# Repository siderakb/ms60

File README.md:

# MS60 Keybaord

60%-size keyboard.

Stabilizer footprints from [ebastler/marbastlib](https://github.com/ebastler/marbastlib).

## License

Licensed under [CERN-OHL-P v2](/LICENSE).

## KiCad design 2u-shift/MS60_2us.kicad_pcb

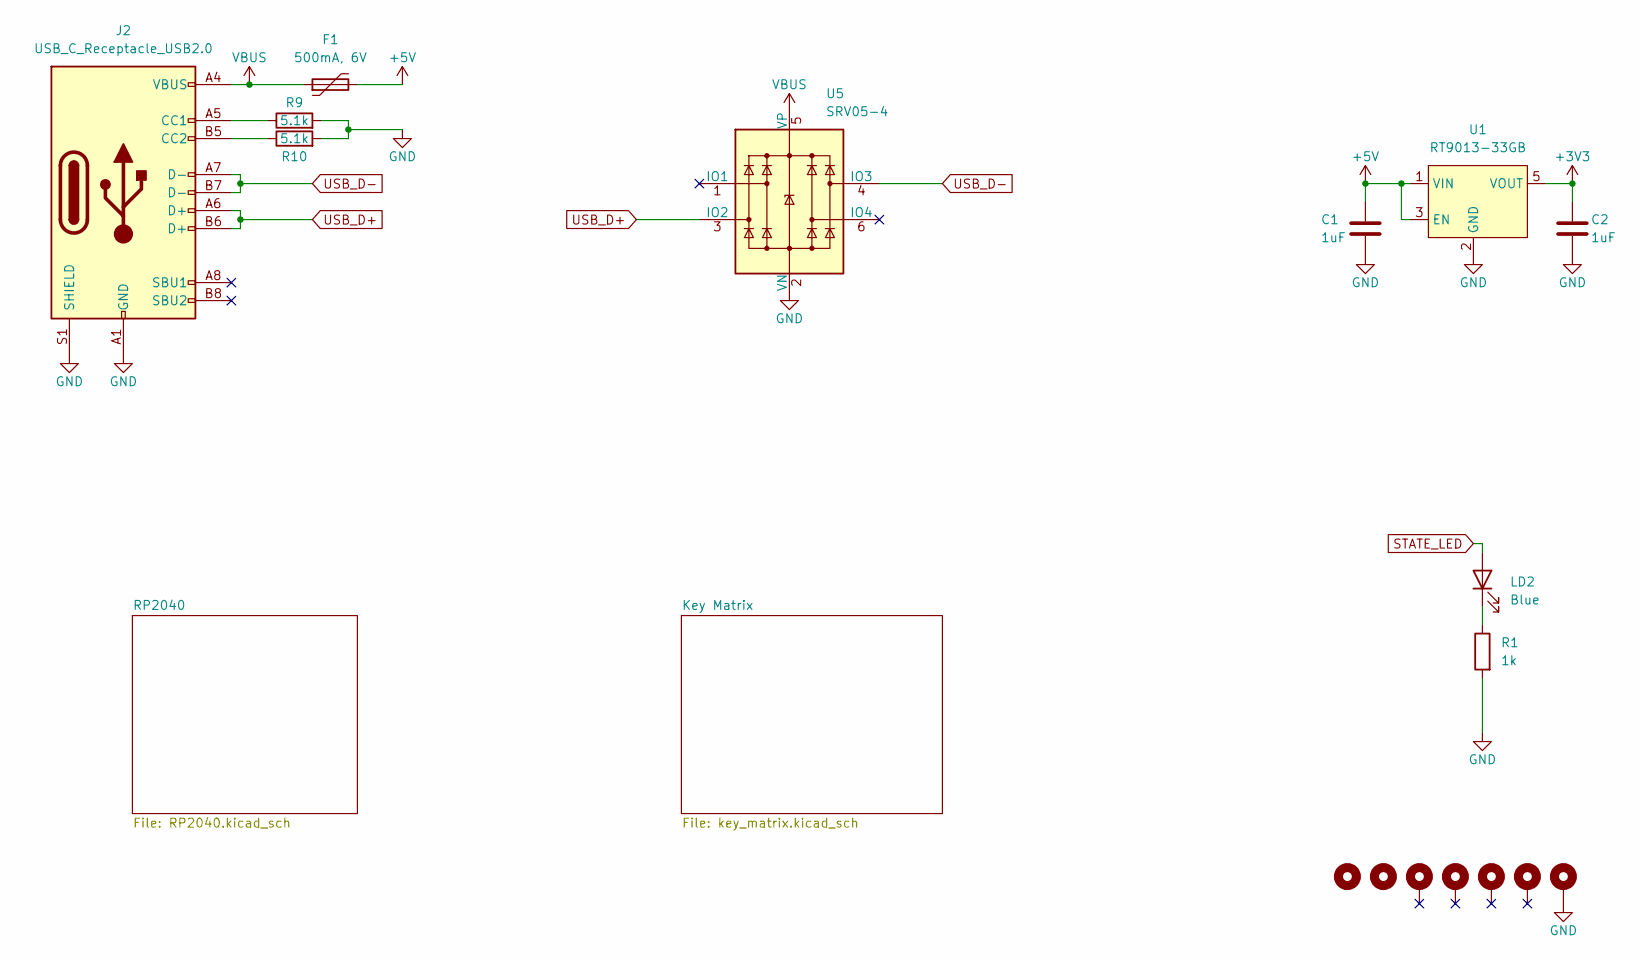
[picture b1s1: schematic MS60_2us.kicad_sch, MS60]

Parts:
C1, C2: 1uF; C_0402_1005Metric; MFR. Part # CL05A105KA5NQNC; LCSC C52923
F1: 500mA, 6V; Fuse_0805_2012Metric; MFR. Part # SMD0805B050TF; LCSC C269104
H1, H7: MountingHole_Pad; MountingHole-D
H2, H3: MountingHole_Pad; MountingHole-A
H4: MountingHole_Pad; MountingHole-B
H5, H6: MountingHole; MountingHole-C
J2: USB_C_Receptacle_USB2.0; USB_C_Receptacle_HRO_TYPE-C-31-M-12; MFR. Part # TYPE-C-31-M-12; LCSC C165948
LD2: Blue; LED_0603_1608Metric; MFR. Part # 19-217/GHC-YR1S2/3T; LCSC C72043
R1: 1k; R_0402_1005Metric; MFR. Part # 0402WGF1001TCE; LCSC C11702
R9, R10: 5.1k; R_0603_1608Metric; MFR. Part # 0402WGF5101TCE; LCSC C25905
U1: RT9013-33GB; SOT-23-5; MFR. Part # TPRT9013-33GB; LCSC C587158
U5: SRV05-4; SOT-23-6; MFR. Part # SRV05-4-P-T7; LCSC C85364

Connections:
+3V3: C2.1, U1.5 (VOUT); also elsewhere on the board
+5V: C1.1, F1.2, U1.1 (VIN), U1.3 (EN)
GND: C1.2, C2.2, H4.1, J2.A1 (GND), J2.A12 (GND), J2.B1 (GND), J2.B12 (GND), J2.S1 (SHIELD), R1.2, R9.2, R10.2, U1.2 (GND), U5.2 (VN); also elsewhere on the board
unnamed: J2.A5 (CC1), R9.1
unnamed: J2.B5 (CC2), R10.1
unnamed: LD2.1 (K), R1.1
STATE_LED: LD2.2 (A); also elsewhere on the board
USB_D+: J2.A6 (D+), J2.B6 (D+), U5.3 (IO2); also elsewhere on the board
USB_D-: J2.A7 (D-), J2.B7 (D-), U5.4 (IO3); also elsewhere on the board
VBUS: F1.1, J2.A4 (VBUS), J2.A9 (VBUS), J2.B4 (VBUS), J2.B9 (VBUS), U5.5 (VP)

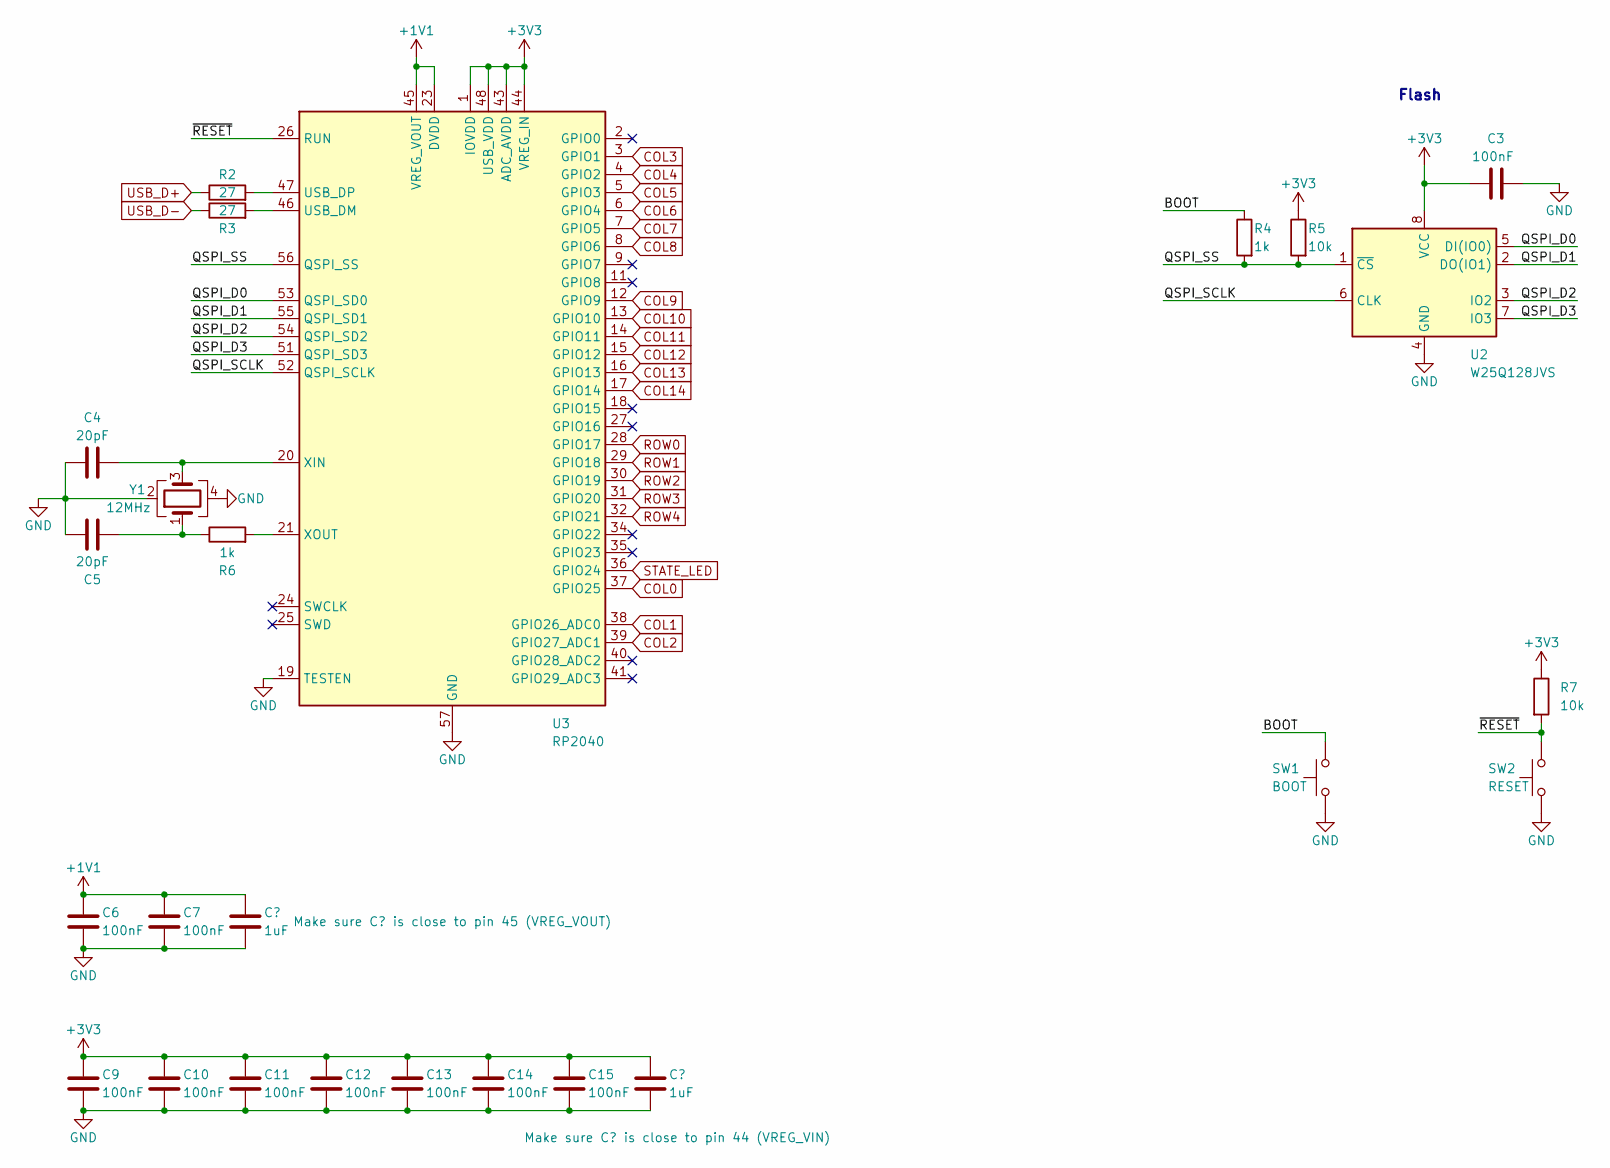
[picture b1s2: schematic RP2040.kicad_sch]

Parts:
C3, C6, C7, C9, C10, C11, C12, C13, C14, C15: 100nF; C_0402_1005Metric; MFR. Part # CL05B104KO5NNNC; LCSC C1525
C4, C5: 20pF; C_0402_1005Metric; MFR. Part # 0402CG200J500NT; LCSC C1554
C8, C16: 1uF; C_0402_1005Metric; MFR. Part # CL05A105KA5NQNC; LCSC C52923
R2, R3: 27; R_0603_1608Metric; MFR. Part # 0603WAF270JT5E; LCSC C25190
R4, R6: 1k; R_0402_1005Metric; MFR. Part # 0402WGF1001TCE; LCSC C11702
R5, R7: 10k; R_0402_1005Metric; MFR. Part # 0402WGF1002TCE; LCSC C25744
SW1: BOOT; SW_SPST_TL3342; MFR. Part # TS-1064S-A1B2-D4; LCSC C498294
SW2: RESET; SW_SPST_TL3342; MFR. Part # TS-1064S-A1B2-D4; LCSC C498294
U2: W25Q128JVS; SOIC-8_5.23x5.23mm_P1.27mm; MFR. Part # W25Q128JVSIQ; LCSC C97521
U3: RP2040; QFN-56-1EP_7x7mm_P0.4mm_EP3.2x3.2mm; MFR. Part # RP2040; LCSC C2040
Y1: 12MHz; Crystal_SMD_3225-4Pin_3.2x2.5mm; MFR. Part # X322512MSB4SI; LCSC C9002

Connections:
+1V1: C6.1, C7.1, C8.1, U3.23 (DVDD), U3.45 (VREG_VOUT), U3.50 (DVDD)
+3V3: C3.1, C9.1, C10.1, C11.1, C12.1, C13.1, C14.1, C15.1, C16.1, R5.1, R7.1, U2.8 (VCC), U3.1 (IOVDD), U3.10 (IOVDD), U3.22 (IOVDD), U3.33 (IOVDD), U3.42 (IOVDD), U3.43 (ADC_AVDD), U3.44 (VREG_IN), U3.48 (USB_VDD), U3.49 (IOVDD); also elsewhere on the board
/RP2040/BOOT: R4.1, SW1.2
/RP2040/QSPI_D0: U2.5 (DI(IO0)), U3.53 (QSPI_SD0)
/RP2040/QSPI_D1: U2.2 (DO(IO1)), U3.55 (QSPI_SD1)
/RP2040/QSPI_D2: U2.3 (IO2), U3.54 (QSPI_SD2)
/RP2040/QSPI_D3: U2.7 (IO3), U3.51 (QSPI_SD3)
/RP2040/QSPI_SCLK: U2.6 (CLK), U3.52 (QSPI_SCLK)
/RP2040/QSPI_SS: R4.2, R5.2, U2.1 (~CS), U3.56 (QSPI_SS)
/RP2040/~RESET: R7.2, SW2.2, U3.26 (RUN)
COL0: U3.37 (GPIO25); also elsewhere on the board
COL1: U3.38 (GPIO26_ADC0); also elsewhere on the board
COL2: U3.39 (GPIO27_ADC1); also elsewhere on the board
COL3: U3.3 (GPIO1); also elsewhere on the board
COL4: U3.4 (GPIO2); also elsewhere on the board
COL5: U3.5 (GPIO3); also elsewhere on the board
COL6: U3.6 (GPIO4); also elsewhere on the board
COL7: U3.7 (GPIO5); also elsewhere on the board
COL8: U3.8 (GPIO6); also elsewhere on the board
COL9: U3.12 (GPIO9); also elsewhere on the board
COL10: U3.13 (GPIO10); also elsewhere on the board
COL11: U3.14 (GPIO11); also elsewhere on the board
COL12: U3.15 (GPIO12); also elsewhere on the board
COL13: U3.16 (GPIO13); also elsewhere on the board
COL14: U3.17 (GPIO14); also elsewhere on the board
GND: C3.2, C4.1, C5.1, C6.2, C7.2, C8.2, C9.2, C10.2, C11.2, C12.2, C13.2, C14.2, C15.2, C16.2, SW1.1, SW2.1, U2.4 (GND), U3.19 (TESTEN), U3.57 (GND), Y1.2, Y1.4; also elsewhere on the board
unnamed: C5.2, R6.1, Y1.1
unnamed: R3.2, U3.46 (USB_DM)
unnamed: R2.2, U3.47 (USB_DP)
unnamed: C4.2, U3.20 (XIN), Y1.3
unnamed: R6.2, U3.21 (XOUT)
ROW0: U3.28 (GPIO17); also elsewhere on the board
ROW1: U3.29 (GPIO18); also elsewhere on the board
ROW2: U3.30 (GPIO19); also elsewhere on the board
ROW3: U3.31 (GPIO20); also elsewhere on the board
ROW4: U3.32 (GPIO21); also elsewhere on the board
STATE_LED: U3.36 (GPIO24); also elsewhere on the board
USB_D+: R2.1; also elsewhere on the board
USB_D-: R3.1; also elsewhere on the board

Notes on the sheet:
Flash

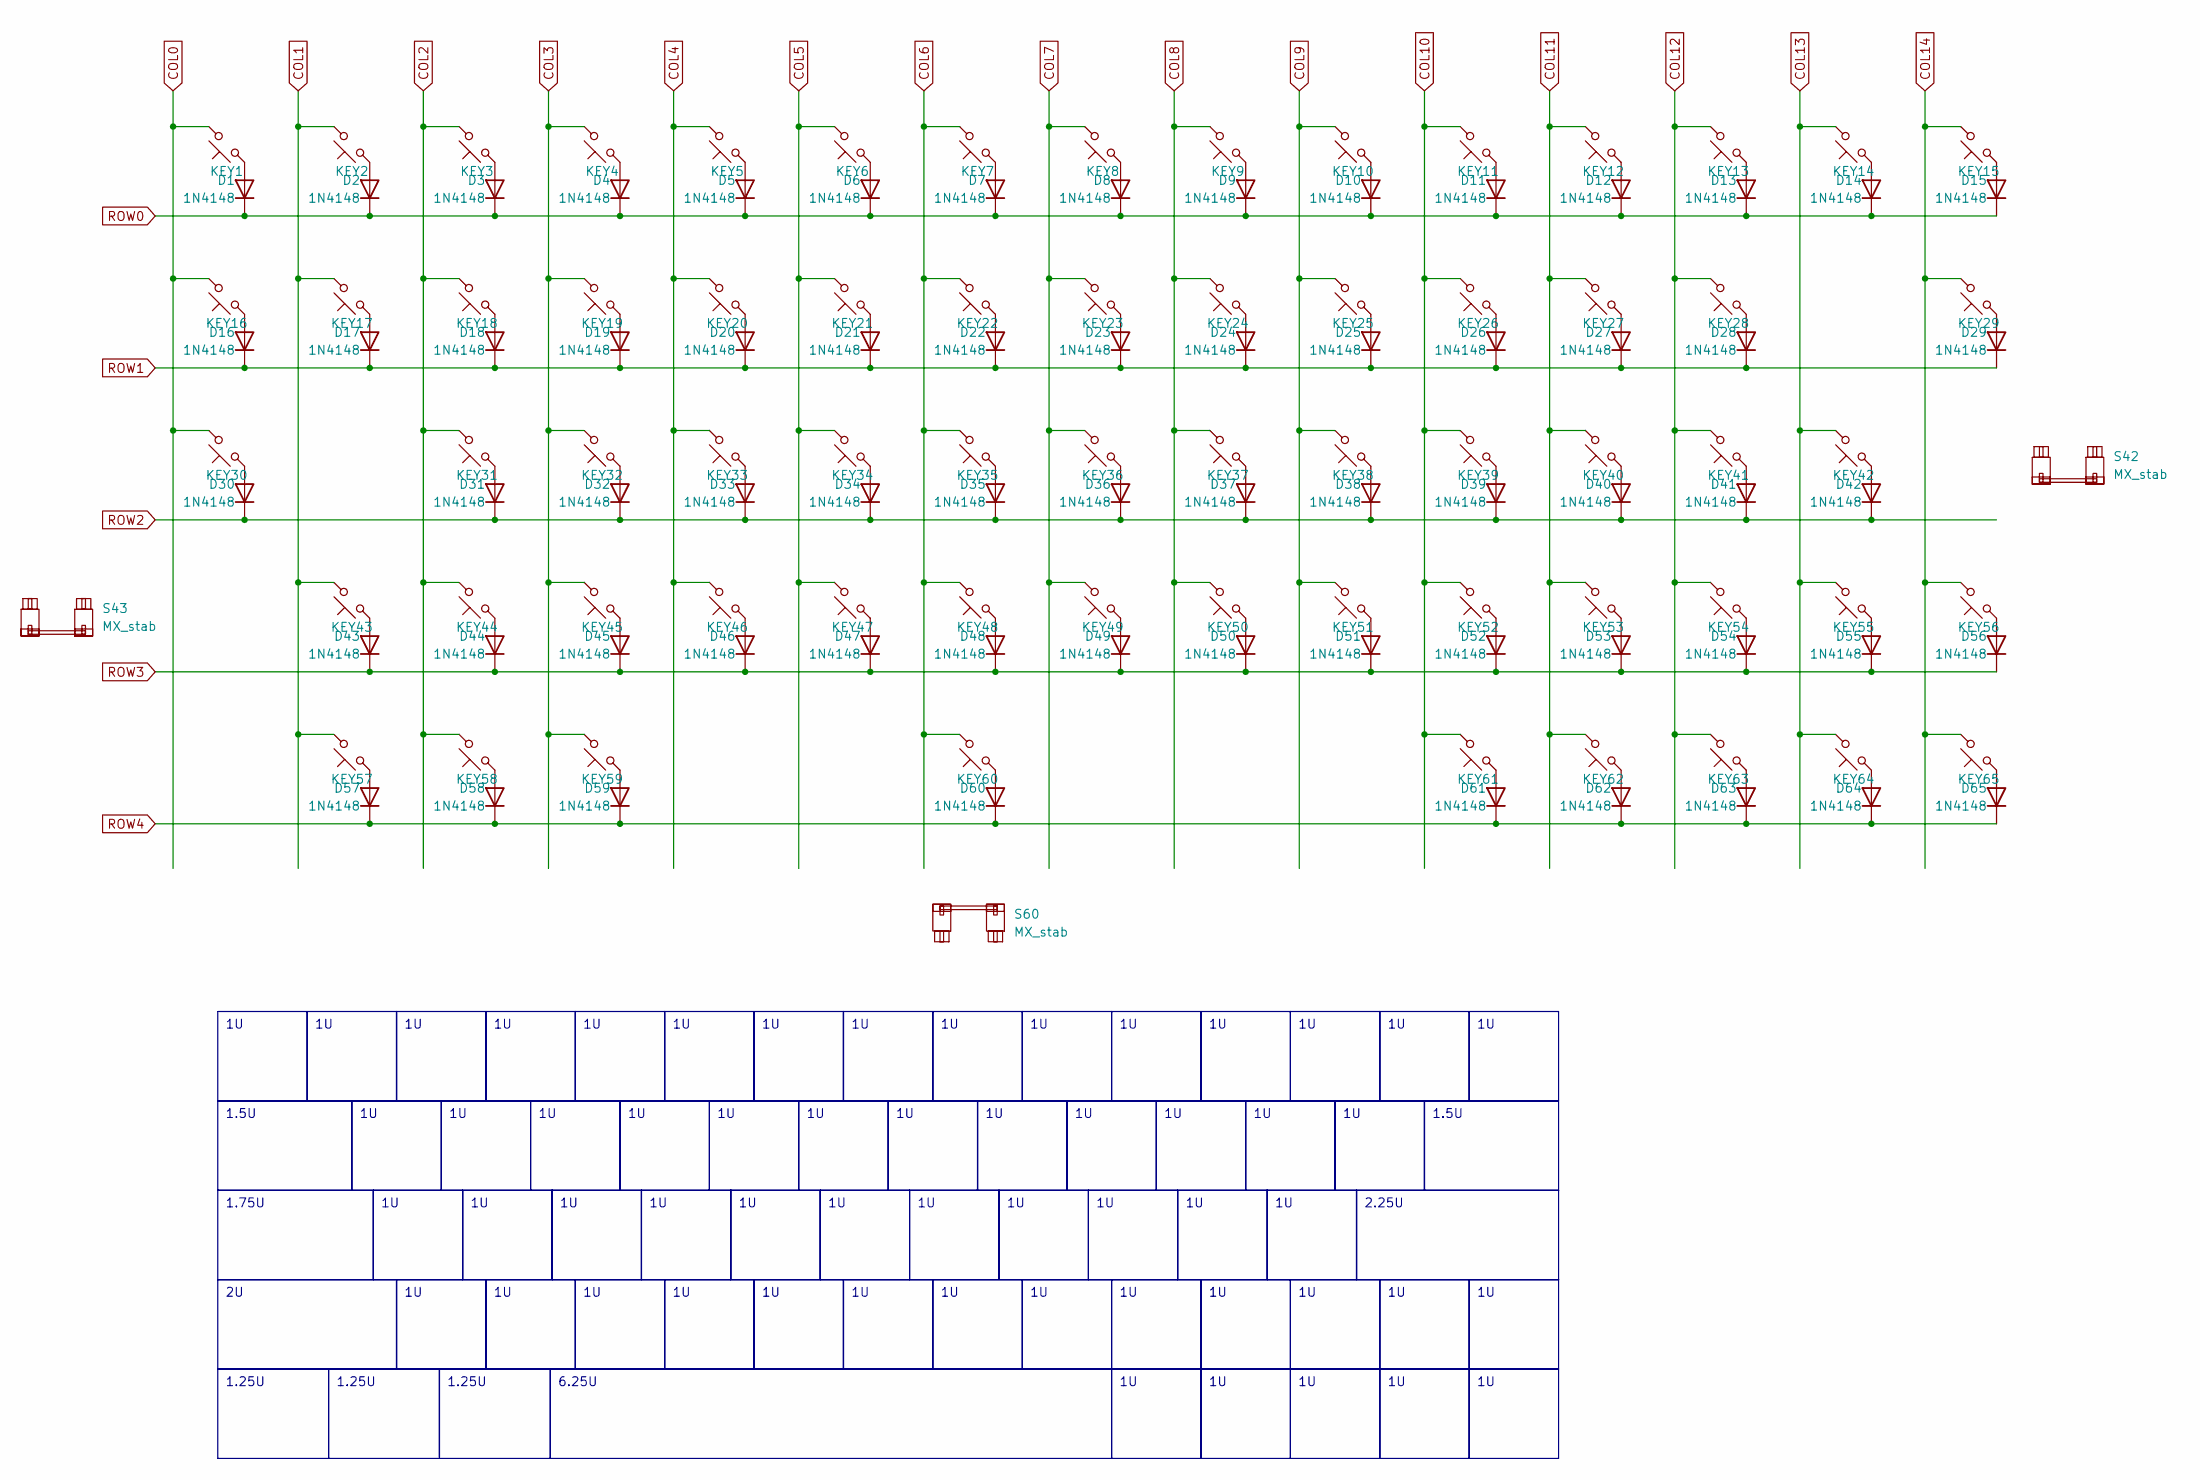
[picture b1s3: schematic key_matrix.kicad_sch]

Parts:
D1, D2, D3, D4, D5, D6, D7, D8, D9, D10, D11, D12, D13, D14, D15, D16, D17, D18, D19, D20, D21, D22, D23, D24, D25, D26, D27, D28, D29, D30, D31, D32, D33, D34, D35, D36, D37, D38, D39, D40, D41, D42, D43, D44, D45, D46, D47, D48, D49, D50, D51, D52, D53, D54, D55, D56, D57, D58, D59, D60, D61, D62, D63, D64, D65: 1N4148; D_SOD-323_HandSoldering; MFR. Part # 1N4148W; LCSC C81598
KEY1, KEY2, KEY3, KEY4, KEY5, KEY6, KEY7, KEY8, KEY9, KEY10, KEY11, KEY12, KEY13, KEY14, KEY15, KEY16, KEY17, KEY18, KEY19, KEY20, KEY21, KEY22, KEY23, KEY24, KEY25, KEY26, KEY27, KEY28, KEY29, KEY30, KEY31, KEY32, KEY33, KEY34, KEY35, KEY36, KEY37, KEY38, KEY39, KEY40, KEY41, KEY42, KEY43, KEY44, KEY45, KEY46, KEY47, KEY48, KEY49, KEY50, KEY51, KEY52, KEY53, KEY54, KEY55, KEY56, KEY57, KEY58, KEY59, KEY60, KEY61, KEY62, KEY63, KEY64, KEY65: SW_Push_45deg; SW_MX_HotSwap_PTH_nSilk
S42: MX_stab; STAB_MX_2.25u
S43: MX_stab; STAB_MX_2u
S60: MX_stab; STAB_MX_6.25u

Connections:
COL0: KEY1.2, KEY16.2, KEY30.2; also elsewhere on the board
COL1: KEY2.2, KEY17.2, KEY43.2, KEY57.2; also elsewhere on the board
COL2: KEY3.2, KEY18.2, KEY31.2, KEY44.2, KEY58.2; also elsewhere on the board
COL3: KEY4.2, KEY19.2, KEY32.2, KEY45.2, KEY59.2; also elsewhere on the board
COL4: KEY5.2, KEY20.2, KEY33.2, KEY46.2; also elsewhere on the board
COL5: KEY6.2, KEY21.2, KEY34.2, KEY47.2; also elsewhere on the board
COL6: KEY7.2, KEY22.2, KEY35.2, KEY48.2, KEY60.2; also elsewhere on the board
COL7: KEY8.2, KEY23.2, KEY36.2, KEY49.2; also elsewhere on the board
COL8: KEY9.2, KEY24.2, KEY37.2, KEY50.2; also elsewhere on the board
COL9: KEY10.2, KEY25.2, KEY38.2, KEY51.2; also elsewhere on the board
COL10: KEY11.2, KEY26.2, KEY39.2, KEY52.2, KEY61.2; also elsewhere on the board
COL11: KEY12.2, KEY27.2, KEY40.2, KEY53.2, KEY62.2; also elsewhere on the board
COL12: KEY13.2, KEY28.2, KEY41.2, KEY54.2, KEY63.2; also elsewhere on the board
COL13: KEY14.2, KEY42.2, KEY55.2, KEY64.2; also elsewhere on the board
COL14: KEY15.2, KEY29.2, KEY56.2, KEY65.2; also elsewhere on the board
unnamed: D1.2 (A), KEY1.1
unnamed: D2.2 (A), KEY2.1
unnamed: D3.2 (A), KEY3.1
unnamed: D4.2 (A), KEY4.1
unnamed: D5.2 (A), KEY5.1
unnamed: D6.2 (A), KEY6.1
unnamed: D7.2 (A), KEY7.1
unnamed: D8.2 (A), KEY8.1
unnamed: D9.2 (A), KEY9.1
unnamed: D10.2 (A), KEY10.1
unnamed: D11.2 (A), KEY11.1
unnamed: D12.2 (A), KEY12.1
unnamed: D13.2 (A), KEY13.1
unnamed: D14.2 (A), KEY14.1
unnamed: D15.2 (A), KEY15.1
unnamed: D16.2 (A), KEY16.1
unnamed: D17.2 (A), KEY17.1
unnamed: D18.2 (A), KEY18.1
unnamed: D19.2 (A), KEY19.1
unnamed: D20.2 (A), KEY20.1
unnamed: D21.2 (A), KEY21.1
unnamed: D22.2 (A), KEY22.1
unnamed: D23.2 (A), KEY23.1
unnamed: D24.2 (A), KEY24.1
unnamed: D25.2 (A), KEY25.1
unnamed: D26.2 (A), KEY26.1
unnamed: D27.2 (A), KEY27.1
unnamed: D28.2 (A), KEY28.1
unnamed: D29.2 (A), KEY29.1
unnamed: D30.2 (A), KEY30.1
unnamed: D31.2 (A), KEY31.1
unnamed: D32.2 (A), KEY32.1
unnamed: D33.2 (A), KEY33.1
unnamed: D34.2 (A), KEY34.1
unnamed: D35.2 (A), KEY35.1
unnamed: D36.2 (A), KEY36.1
unnamed: D37.2 (A), KEY37.1
unnamed: D38.2 (A), KEY38.1
unnamed: D39.2 (A), KEY39.1
unnamed: D40.2 (A), KEY40.1
unnamed: D41.2 (A), KEY41.1
unnamed: D42.2 (A), KEY42.1
unnamed: D43.2 (A), KEY43.1
unnamed: D44.2 (A), KEY44.1
unnamed: D45.2 (A), KEY45.1
unnamed: D46.2 (A), KEY46.1
unnamed: D47.2 (A), KEY47.1
unnamed: D48.2 (A), KEY48.1
unnamed: D49.2 (A), KEY49.1
unnamed: D50.2 (A), KEY50.1
unnamed: D51.2 (A), KEY51.1
unnamed: D52.2 (A), KEY52.1
unnamed: D53.2 (A), KEY53.1
unnamed: D54.2 (A), KEY54.1
unnamed: D55.2 (A), KEY55.1
unnamed: D56.2 (A), KEY56.1
unnamed: D57.2 (A), KEY57.1
unnamed: D58.2 (A), KEY58.1
unnamed: D59.2 (A), KEY59.1
unnamed: D60.2 (A), KEY60.1
unnamed: D61.2 (A), KEY61.1
unnamed: D62.2 (A), KEY62.1
unnamed: D63.2 (A), KEY63.1
unnamed: D64.2 (A), KEY64.1
unnamed: D65.2 (A), KEY65.1
ROW0: D1.1 (K), D2.1 (K), D3.1 (K), D4.1 (K), D5.1 (K), D6.1 (K), D7.1 (K), D8.1 (K), D9.1 (K), D10.1 (K), D11.1 (K), D12.1 (K), D13.1 (K), D14.1 (K), D15.1 (K); also elsewhere on the board
ROW1: D16.1 (K), D17.1 (K), D18.1 (K), D19.1 (K), D20.1 (K), D21.1 (K), D22.1 (K), D23.1 (K), D24.1 (K), D25.1 (K), D26.1 (K), D27.1 (K), D28.1 (K), D29.1 (K); also elsewhere on the board
ROW2: D30.1 (K), D31.1 (K), D32.1 (K), D33.1 (K), D34.1 (K), D35.1 (K), D36.1 (K), D37.1 (K), D38.1 (K), D39.1 (K), D40.1 (K), D41.1 (K), D42.1 (K); also elsewhere on the board
ROW3: D43.1 (K), D44.1 (K), D45.1 (K), D46.1 (K), D47.1 (K), D48.1 (K), D49.1 (K), D50.1 (K), D51.1 (K), D52.1 (K), D53.1 (K), D54.1 (K), D55.1 (K), D56.1 (K); also elsewhere on the board
ROW4: D57.1 (K), D58.1 (K), D59.1 (K), D60.1 (K), D61.1 (K), D62.1 (K), D63.1 (K), D64.1 (K), D65.1 (K); also elsewhere on the board

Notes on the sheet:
1.5U
2.25U
1.25U
6.25U
1.75U

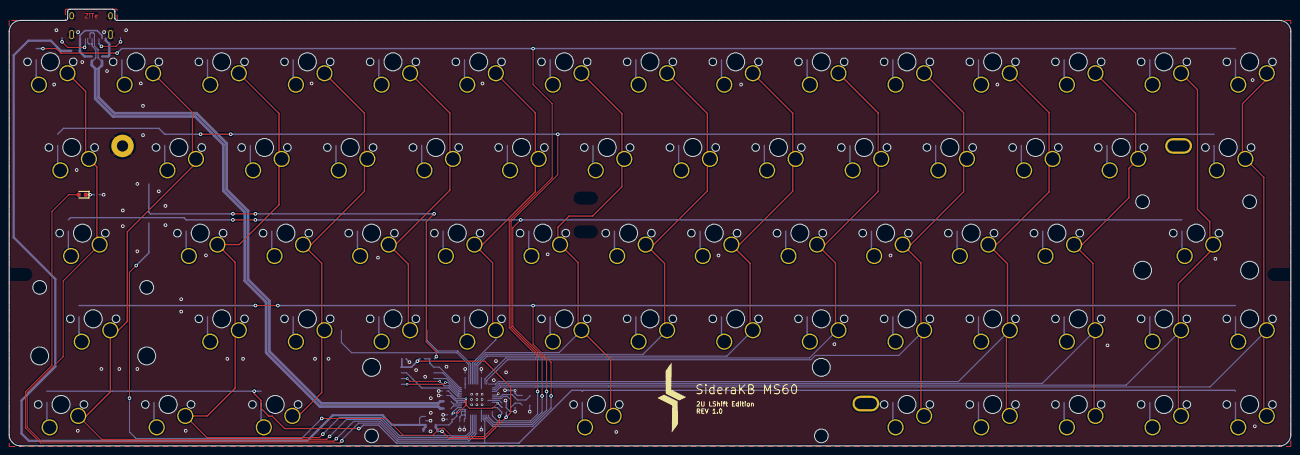
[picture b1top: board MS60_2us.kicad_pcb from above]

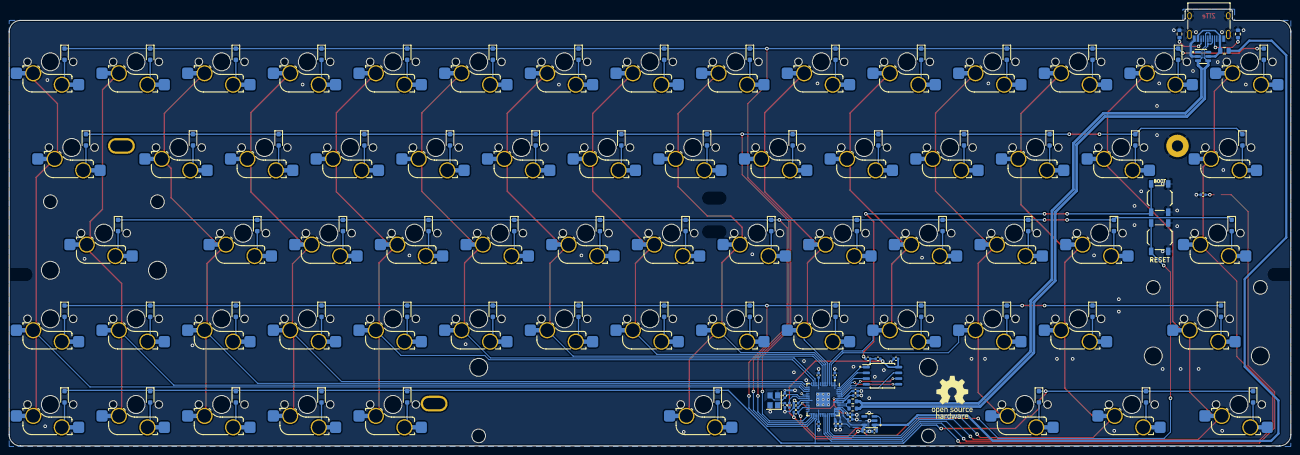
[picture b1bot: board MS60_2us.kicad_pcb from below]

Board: 2 copper layers, 285.0 x 97.1 mm, 175 parts (99 on the bottom side), 109 nets.

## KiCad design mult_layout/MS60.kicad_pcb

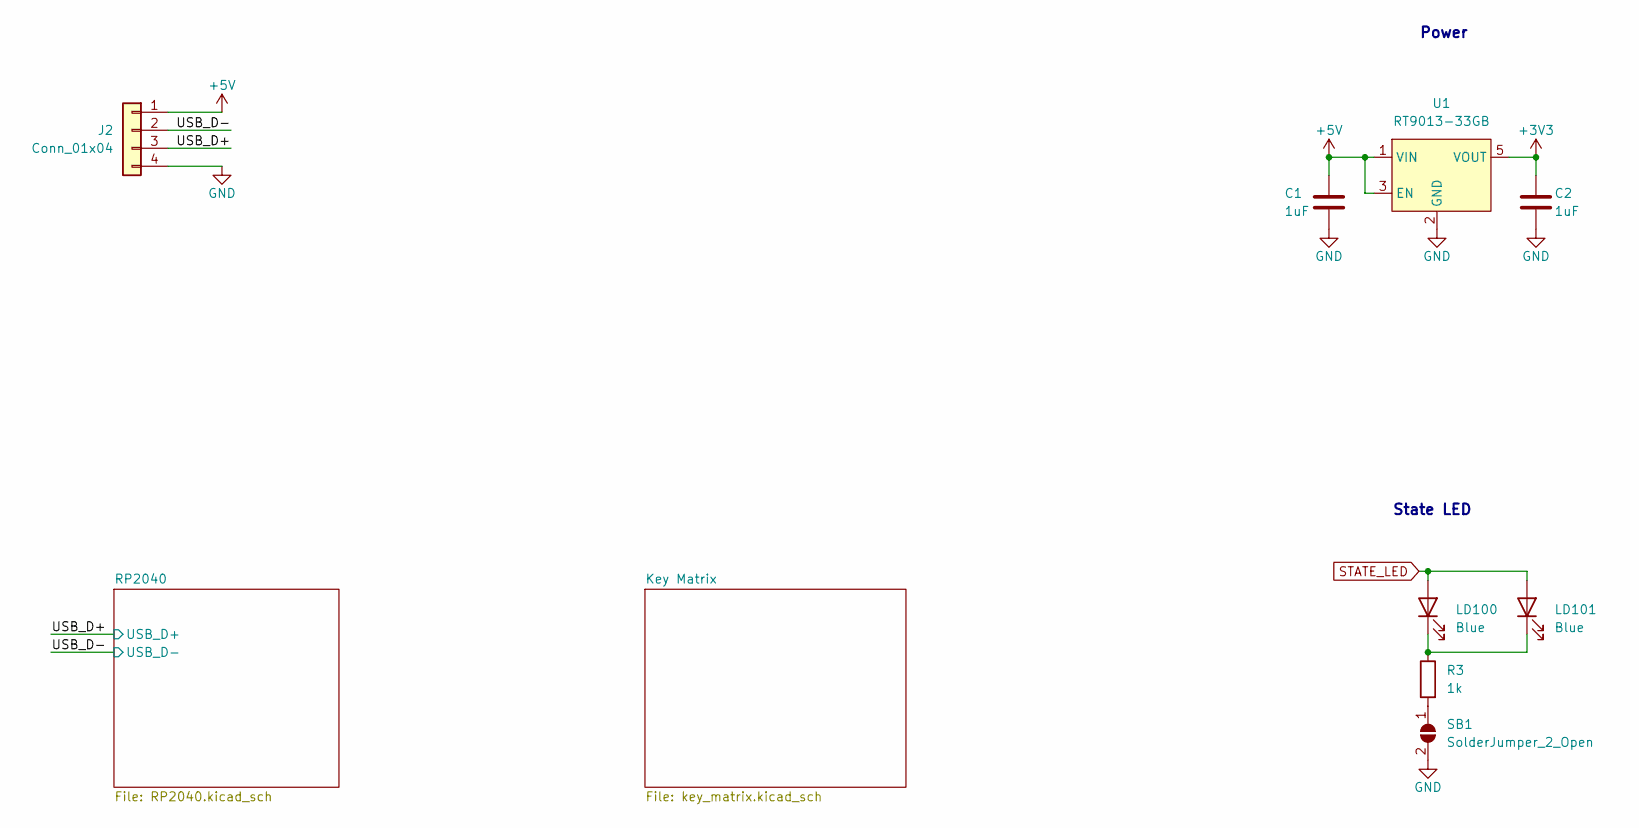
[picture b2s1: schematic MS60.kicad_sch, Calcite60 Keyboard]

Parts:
C1, C2: 1uF; C_0402_1005Metric; MFR. Part # CL05A105KA5NQNC; LCSC C52923
J2: Conn_01x04; Molex_Pico-EZmate_78171-0004_1x04-1MP_P1.20mm_Vertical
LD100, LD101: Blue; LED_0603_1608Metric; MFR. Part # 19-217/GHC-YR1S2/3T; LCSC C72043
R3: 1k; R_0402_1005Metric; MFR. Part # 0402WGF1001TCE; LCSC C11702
SB1: SolderJumper_2_Open; SolderJumper-2_P1.3mm_Open_TrianglePad1.0x1.5mm
U1: RT9013-33GB; SOT-23-5; MFR. Part # TPRT9013-33GB; LCSC C587158

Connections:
/USB_D+: J2.3; also elsewhere on the board
/USB_D-: J2.2; also elsewhere on the board
unnamed: LD100.1 (K), LD101.1 (K), R3.1
unnamed: R3.2, SB1.1 (A)
STATE_LED: LD100.2 (A), LD101.2 (A); also elsewhere on the board

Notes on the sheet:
State LED
Power

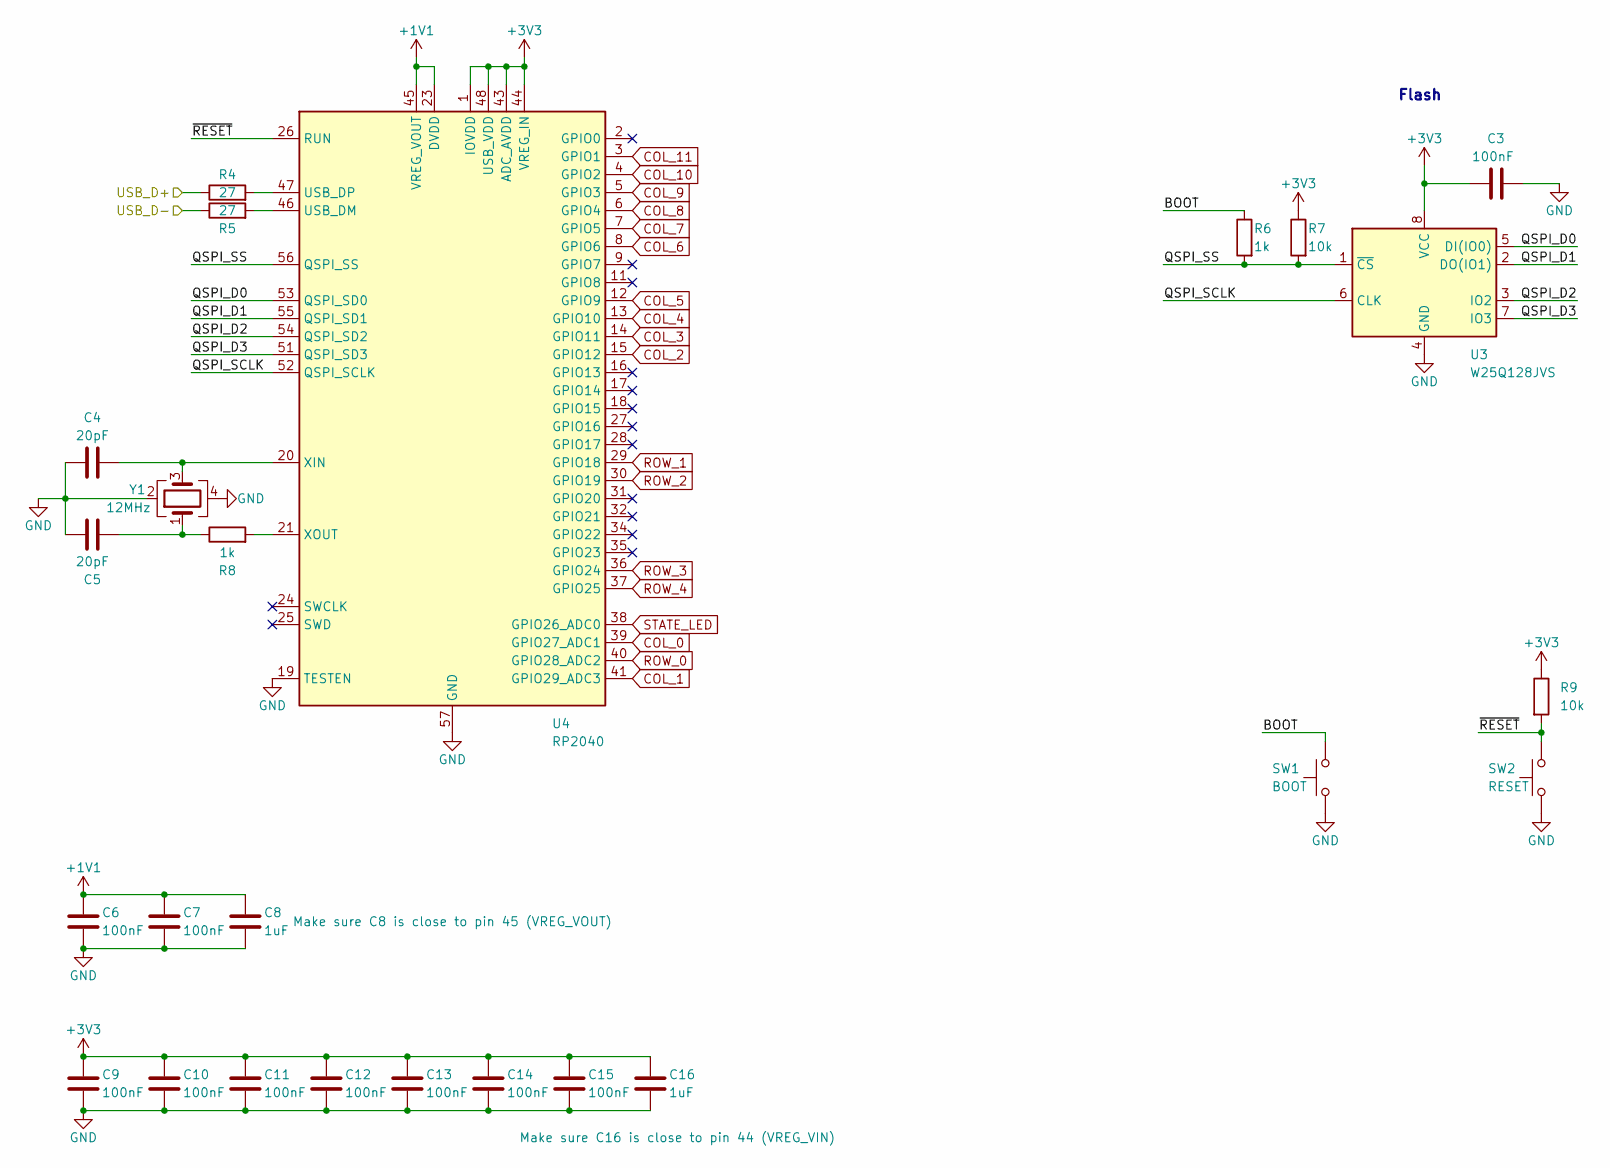
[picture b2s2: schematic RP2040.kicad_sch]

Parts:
C3, C6, C7, C9, C10, C11, C12, C13, C14, C15: 100nF; C_0402_1005Metric; MFR. Part # CL05B104KO5NNNC; LCSC C1525
C4, C5: 20pF; C_0402_1005Metric; MFR. Part # 0402CG200J500NT; LCSC C1554
C8, C16: 1uF; C_0402_1005Metric; MFR. Part # CL05A105KA5NQNC; LCSC C52923
R4, R5: 27; R_0603_1608Metric; MFR. Part # 0603WAF270JT5E; LCSC C25190
R6, R8: 1k; R_0402_1005Metric; MFR. Part # 0402WGF1001TCE; LCSC C11702
R7, R9: 10k; R_0402_1005Metric; MFR. Part # 0402WGF1002TCE; LCSC C25744
SW1: BOOT; SW_SPST_B3U-1000P; MFR. Part # TS-1064S-A1B2-D4; LCSC C498294
SW2: RESET; SW_SPST_B3U-1000P; MFR. Part # TS-1064S-A1B2-D4; LCSC C498294
U3: W25Q128JVS; SOIC-8_5.23x5.23mm_P1.27mm; MFR. Part # W25Q128JVSIQ; LCSC C97521
U4: RP2040; QFN-56-1EP_7x7mm_P0.4mm_EP3.2x3.2mm; MFR. Part # RP2040; LCSC C2040
Y1: 12MHz; Crystal_SMD_3225-4Pin_3.2x2.5mm; MFR. Part # X322512MSB4SI; LCSC C9002

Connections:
/RP2040/BOOT: R6.1, SW1.2
/RP2040/QSPI_D0: U3.5 (DI(IO0)), U4.53 (QSPI_SD0)
/RP2040/QSPI_D1: U3.2 (DO(IO1)), U4.55 (QSPI_SD1)
/RP2040/QSPI_D2: U3.3 (IO2), U4.54 (QSPI_SD2)
/RP2040/QSPI_D3: U3.7 (IO3), U4.51 (QSPI_SD3)
/RP2040/QSPI_SCLK: U3.6 (CLK), U4.52 (QSPI_SCLK)
/RP2040/QSPI_SS: R6.2, R7.2, U3.1 (~CS), U4.56 (QSPI_SS)
/RP2040/~RESET: R9.2, SW2.2, U4.26 (RUN)
/USB_D+: R4.1; also elsewhere on the board
/USB_D-: R5.1; also elsewhere on the board
COL_0: U4.39 (GPIO27_ADC1)
COL_1: U4.41 (GPIO29_ADC3)
COL_2: U4.15 (GPIO12)
COL_3: U4.14 (GPIO11)
COL_4: U4.13 (GPIO10)
COL_5: U4.12 (GPIO9)
COL_6: U4.8 (GPIO6)
COL_7: U4.7 (GPIO5)
COL_8: U4.6 (GPIO4)
COL_9: U4.5 (GPIO3)
COL_10: U4.4 (GPIO2)
COL_11: U4.3 (GPIO1)
unnamed: C5.2, R8.1, Y1.1
unnamed: R5.2, U4.46 (USB_DM)
unnamed: R4.2, U4.47 (USB_DP)
unnamed: C4.2, U4.20 (XIN), Y1.3
unnamed: R8.2, U4.21 (XOUT)
ROW_0: U4.40 (GPIO28_ADC2)
ROW_1: U4.29 (GPIO18)
ROW_2: U4.30 (GPIO19)
ROW_3: U4.36 (GPIO24)
ROW_4: U4.37 (GPIO25)
STATE_LED: U4.38 (GPIO26_ADC0); also elsewhere on the board

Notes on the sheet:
Flash

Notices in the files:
2u-shift/MS60_2us.kicad_pcb:
Open source hardware, CERN-OHL-P v2
mult_layout/MS60.kicad_sch:
MIT License (Open source hardware)
